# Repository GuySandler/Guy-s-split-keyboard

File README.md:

# Guy's-split-keyboard

My first project I am making on my own. A basic wireless split keyboard

# BOM:

| Amount          | Name                                     | Source                                                                                                                                      | Price |
|-----------------|------------------------------------------|---------------------------------------------------------------------------------------------------------------------------------------------|-------|
| 2               | XIAO-nRF52840                            | [aliexpress](https://www.aliexpress.us/item/3256806802639384.html) not including $7.72 shipping                                             | 17.98 |
| 42 (min 50)     | Gateron Low Profile Switch 2.0           | [aliexpress](https://www.aliexpress.us/item/3256806684099095.html)                                                                          | 16.79 |
| 2               | 103450 3.7V 2000mAh Polymer Lithium      | [aliexpress](https://www.aliexpress.us/item/3256809404408618.html)                                                                          | 9.65  |
| 42 (min 50)     | IN4148 DO-35 High-Speed Switching Diodes | [aliexpress](https://www.aliexpress.us/item/3256809192784213.html) (buying 100 is .48 more than buying 50)                                  | 1.95  |
| 2               | 47 Ohms resistors                        | I have some left from #solder                                                                                                               | 0     |
| 4               | M3x16 Bolt                               | I have some from a previous hackpad                                                                                                         | 0     |
| 4               | M3 Heatset                               | I have some from a previous hackpad                                                                                                         | 0     |
| 42              | keycaps                                  | I am resin printing mine and found [these models](https://www.printables.com/model/158865-chicago-steno-low-profile-keycaps-kailh-choc/)    | X     |
| 1               | bottom 3d printed case                   | I am FDM printing mine, model found in CAD folder                                                                                           | X     |

# Picturess

| Label           | Image                                            |
|-----------------|--------------------------------------------------|
| Schematic       |          |
| PCB             |                |
| CAD             |       |
| JLC Cart        |            |
| JLC + Shipping  |           |
| Aliexpress Cart |     |

# Total Price (without 3d printed parts)
## $75.29
- 28.09 JLC + 47.2 Aliexpress

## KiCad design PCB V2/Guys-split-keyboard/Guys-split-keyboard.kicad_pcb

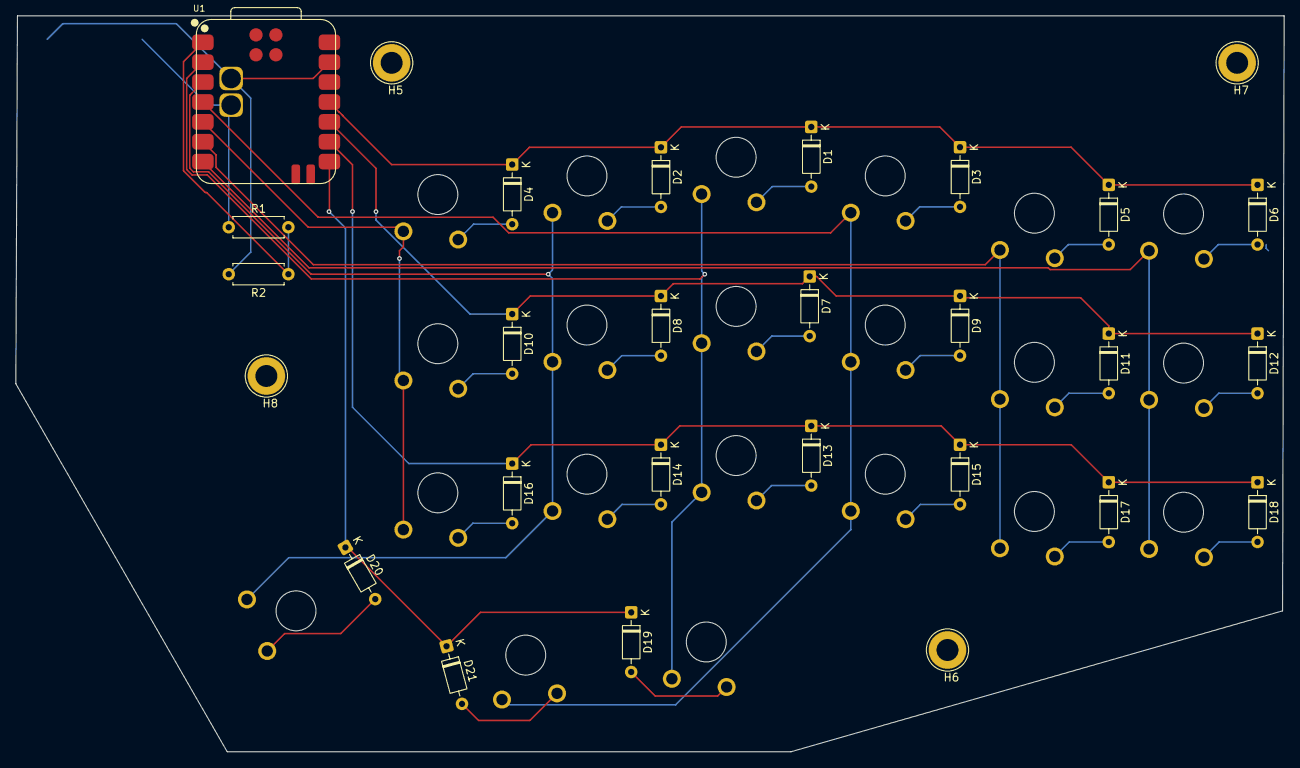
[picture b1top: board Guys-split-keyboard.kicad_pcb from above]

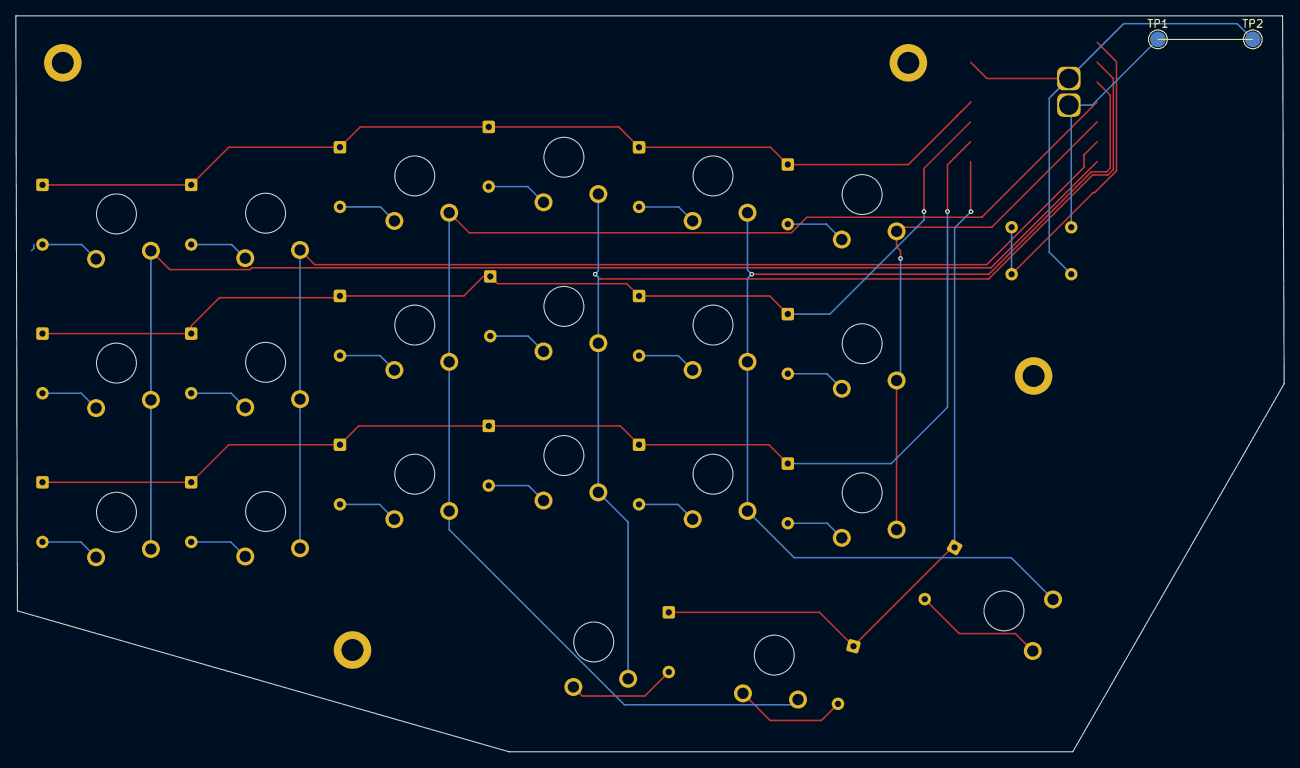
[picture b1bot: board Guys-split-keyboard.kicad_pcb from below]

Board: 2 copper layers, 162.0 x 94.0 mm, 55 parts (2 on the bottom side), 34 nets.

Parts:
D1, D2, D3, D4, D5, D6, D7, D8, D9, D10, D11, D12, D13, D14, D15, D16, D17, D18, D19, D20, D21: D; D_DO-35_SOD27_P7.62mm_Horizontal
H1, H2, H3, H4: MountingHole; mouse-bite-5mm-slot
H5, H6, H7, H8: MountingHole; TestPoint_Loop_D3.80mm_Drill2.8mm
R1, R2: R; R_Axial_DIN0207_L6.3mm_D2.5mm_P7.62mm_Horizontal
SW1, SW2, SW3, SW4, SW5, SW6, SW7, SW8, SW9, SW10, SW11, SW12, SW13, SW14, SW15, SW16, SW17, SW18, SW19, SW21: SW_Push; Gateron-KS33-Solderable-1U
SW20: SW_Push; Gateron-KS33-Solderable-2U
TP1: BAT; TestPoint_Pad_D2.0mm
TP2: GND; TestPoint_Pad_D2.0mm
U1: XIAO-nRF52840-SMD; modified-XIAO-nRF52840-SMD

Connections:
BTPin: R1.2, R2.1, U1.1 (P0.02_A0_D0)
Col1: SW1.1, SW7.1, SW13.1, SW19.1, U1.2 (P0.03_A1_D1)
Col2: SW2.1, SW8.1, SW14.1, SW20.1, U1.3 (P0.28_A2_D2)
Col3: SW3.1, SW9.1, SW15.1, SW21.1, U1.4 (P0.29_A3_D3)
Col4: SW4.1, SW10.1, SW16.1, U1.5 (P0.04_A4_D4_SDA)
Col5: SW5.1, SW11.1, SW17.1, U1.6 (P0.05_A5_D5_SCL)
Col6: SW6.1, SW12.1, SW18.1, U1.7 (P1.11_D6_TX)
GND: R2.2, TP2.1, U1.13 (GND), U1.16 (GND)
unnamed: D1.2 (A), SW1.2
unnamed: D2.2 (A), SW2.2
unnamed: D3.2 (A), SW3.2
unnamed: D4.2 (A), SW4.2
unnamed: D5.2 (A), SW5.2
unnamed: D6.2 (A), SW6.2
unnamed: D7.2 (A), SW7.2
unnamed: D8.2 (A), SW8.2
unnamed: D9.2 (A), SW9.2
unnamed: D10.2 (A), SW10.2
unnamed: D11.2 (A), SW11.2
unnamed: D12.2 (A), SW12.2
unnamed: D13.2 (A), SW13.2
unnamed: D14.2 (A), SW14.2
unnamed: D15.2 (A), SW15.2
unnamed: D16.2 (A), SW16.2
unnamed: D17.2 (A), SW17.2
unnamed: D18.2 (A), SW18.2
unnamed: D19.2 (A), SW19.2
unnamed: D20.2 (A), SW20.2
unnamed: D21.2 (A), SW21.2
Row1: D1.1 (K), D2.1 (K), D3.1 (K), D4.1 (K), D5.1 (K), D6.1 (K), U1.11 (P1.15_D10_MOSI)
Row2: D7.1 (K), D8.1 (K), D9.1 (K), D10.1 (K), D11.1 (K), D12.1 (K), U1.10 (P1.14_D9_MISO)
Row3: D13.1 (K), D14.1 (K), D15.1 (K), D16.1 (K), D17.1 (K), D18.1 (K), U1.9 (P1.13_D8_SCK)
Row4: D19.1 (K), D20.1 (K), D21.1 (K), U1.8 (P1.12_D7_RX)
VBAT: R1.1, TP1.1, U1.15 (BAT)

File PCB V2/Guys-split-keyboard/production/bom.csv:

Designator,Footprint,Quantity,Value,LCSC Part #
"D1_2, D1, D10_2, D10, D11_2, D11, D12_2, D12, D13_2, D13, D14_2, D14, D15_2, D15, D16_2, D16, D17_2, D17, D18_2, D18, D19_2, D19, D2_2, D2, D20_2, D20, D21_2, D21, D3_2, D3, D4_2, D4, D5_2, D5, D6_2, D6, D7_2, D7, D8_2, D8, D9_2, D9",D_DO-35_SOD27_P7.62mm_Horizontal,42,D,
"R1_2, R1, R2_2, R2",R_Axial_DIN0207_L6.3mm_D2.5mm_P7.62mm_Horizontal,4,R,
"SW1_2, SW1, SW10_2, SW10, SW11_2, SW11, SW12_2, SW12, SW13_2, SW13, SW14_2, SW14, SW15_2, SW15, SW16_2, SW16, SW17_2, SW17, SW18_2, SW18, SW19_2, SW19, SW2_2, SW2, SW20_2, SW20, SW21_2, SW21, SW3_2, SW3, SW4_2, SW4, SW5_2, SW5, SW6_2, SW6, SW7_2, SW7, SW9_2, SW9",Gateron-KS33-Solderable-1U,40,SW_Push,
"SW8_2, SW8",Gateron-KS33-Solderable-2U,2,SW_Push,
"TP1_2, TP1",TestPoint_Pad_D2.0mm,2,BAT,
"TP2_2, TP2",TestPoint_Pad_D2.0mm,2,GND,
"U1_2, U1",modified-XIAO-nRF52840-SMD,2,XIAO-nRF52840-SMD,

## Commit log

2025-11-20 init
2025-11-21 work
2025-11-23 some more work
2025-11-25 pcb V1 and V2
2025-11-25 I forgot the other half, todo later
2025-11-26 added other half
2025-11-26 firmware framework done
2025-11-26 just case left
2025-11-27 quick fix
2025-11-27 top done
2025-11-27 done + quick fix
2025-11-28 lowered xiao price
